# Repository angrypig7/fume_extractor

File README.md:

View this project on [CADLAB.io](https://cadlab.io/project/2056). 

# fume_extractor
portable soldering fume extractor

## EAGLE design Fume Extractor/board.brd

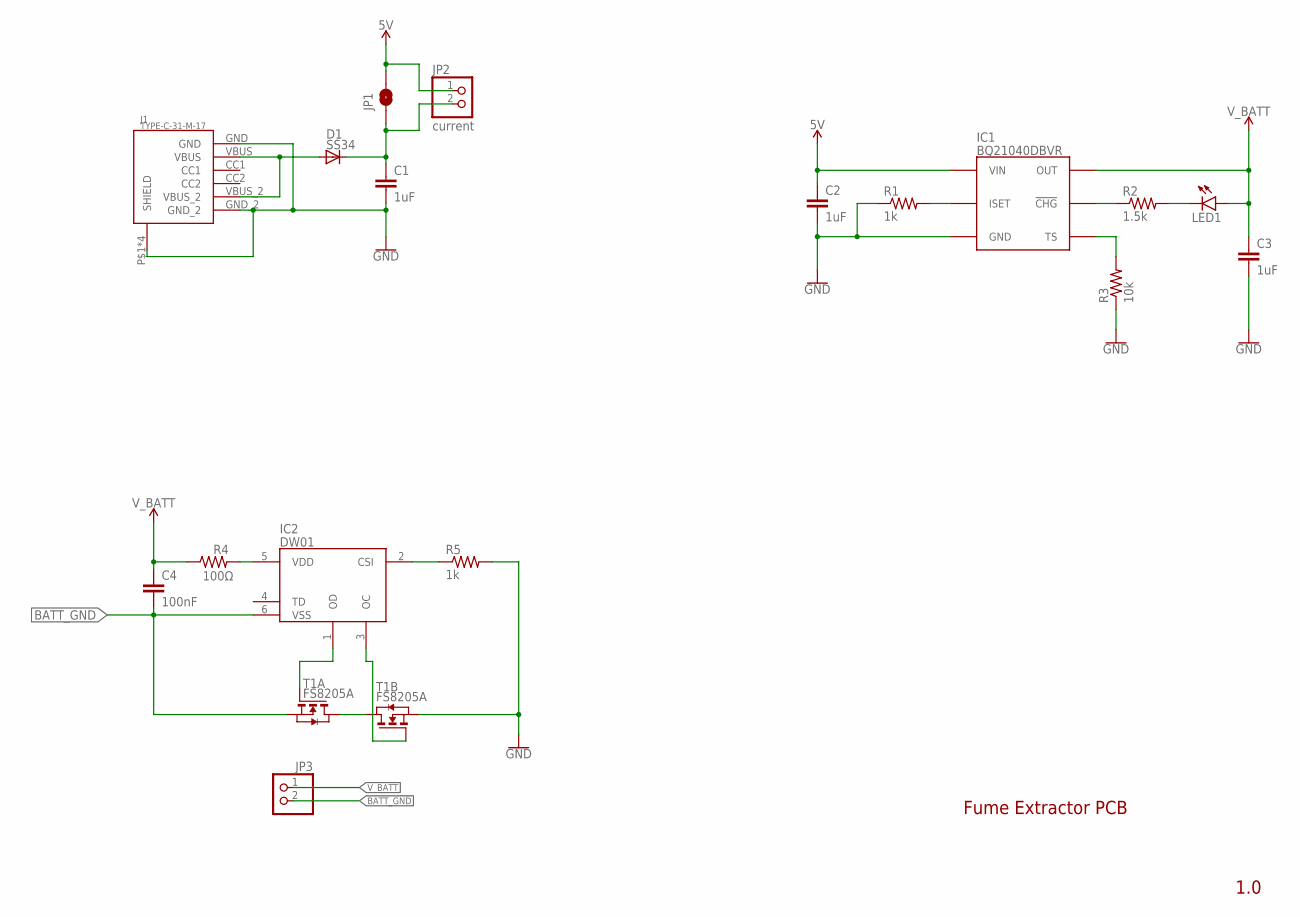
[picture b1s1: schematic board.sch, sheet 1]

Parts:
C1, C2, C3: 1uF; C0603
C4: 100nF; C0603
D1: SS34; DO214AC
IC1: BQ21040DBVR; SOT95P280X145-6N
IC2: DW01; SOT95P280X135-6N
J1: TYPE-C-31-M-17
JP1: JUMPER-SMT_2_NO_NO-SILK; SMT-JUMPER_2_NO_NO-SILK
JP2: current; 1X02/OCT
JP3: PINHD-1X2/OCT; 1X02/OCT
LED1: LEDCHIP-LED0805; CHIP-LED0805
R1, R5: 1k; R0603
R2: 1.5k; R0603
R3: 10k; R0603
R4: 100Ω; R0603
T1: FS8205A; TSSOP-8

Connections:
5V: C2.1, IC1.6 (VIN), JP1.2, JP2.1; also elsewhere on the board
BATT_GND: C4.2, IC2.6 (VSS), JP3.2, T1.2 (S), T1.3 (S)
GND: C1.2, C2.2, C3.2, IC1.5 (GND), J1.GND, J1.GND_2, J1.P$1 (SHIELD), J1.P$2 (SHIELD), J1.P$3 (SHIELD), J1.P$4 (SHIELD), R1.1, R3.1, R5.2, T1.6 (S), T1.7 (S); also elsewhere on the board
unnamed: IC2.5 (VDD), R4.2
unnamed: IC1.1 (TS), R3.2
unnamed: IC1.3 (!CHG), R2.1
unnamed: IC2.2 (CSI), R5.1
unnamed: T1.1 (D), T1.8 (D)
unnamed: IC2.1 (OD), T1.4 (G)
unnamed: IC2.3 (OC), T1.5 (G)
unnamed: LED1.C, R2.2
unnamed: IC1.4 (ISET), R1.2
unnamed: C1.1, D1.C, JP1.1, JP2.2
unnamed: D1.A, J1.VBUS, J1.VBUS_2
V_BATT: C3.1, C4.1, IC1.2 (OUT), JP3.1, LED1.A, R4.1

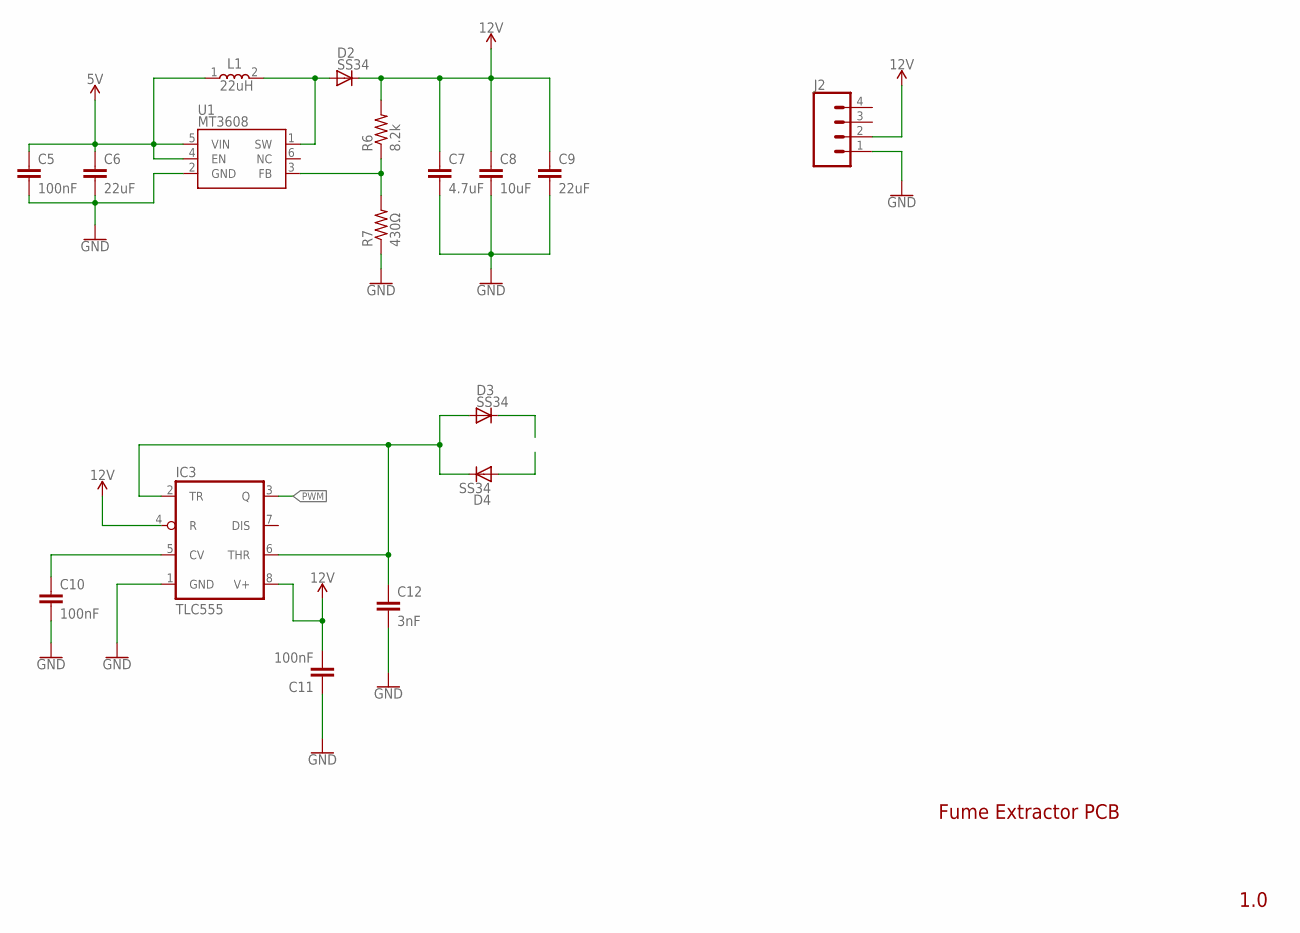
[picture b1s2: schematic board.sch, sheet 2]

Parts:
C5, C10, C11: 100nF; C0603
C6, C9: 22uF; C0805
C7: 4.7uF; C0603
C8: 10uF; C0805
C12: 3nF; C0603
D2, D3, D4: SS34; DO214AC
IC3: TLC555; SO08
J2: CONN_04POLAR_LOCK; MOLEX-1X4_LOCK
L1: 22uH; INDPM7066X300N
R6: 8.2k; R0603
R7: 430Ω; R0603
U1: MT3608; SOT23-6

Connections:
5V: C5.1, C6.1, L1.1, U1.4 (EN), U1.5 (VIN); also elsewhere on the board
12V: C7.1, C8.1, C9.1, C11.2, D2.C, IC3.4 (R), IC3.8 (V+), J2.2, R6.2
GND: C5.2, C6.2, C7.2, C8.2, C9.2, C10.2, C11.1, C12.2, IC3.1 (GND), J2.1, R7.1, U1.2 (GND); also elsewhere on the board
unnamed: D2.A, L1.2, U1.1 (SW)
unnamed: C10.1, IC3.5 (CV)
unnamed: R6.1, R7.2, U1.3 (FB)
unnamed: C12.1, D3.A, D4.C, IC3.2 (TR), IC3.6 (THR)
PWM: IC3.3 (Q)

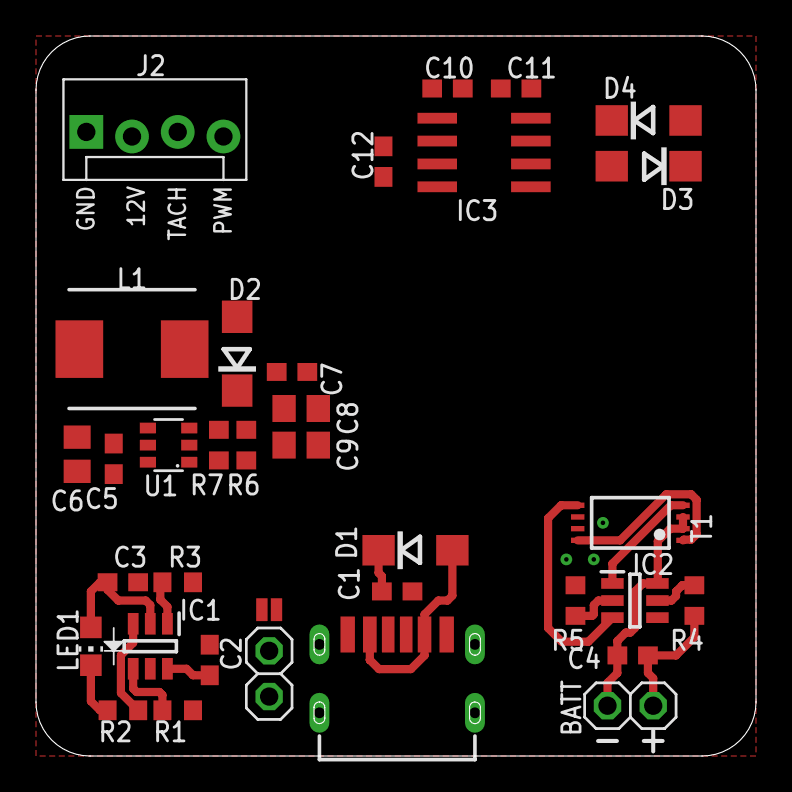
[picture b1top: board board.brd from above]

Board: 2 copper layers, 40.0 x 40.0 mm, 35 parts (0 on the bottom side), 20 nets.

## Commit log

2019-07-27 battery charging circuit
2019-07-28 battery charging + protection circuit
2019-08-14 MCP72831 circuit backup, TP4056
2019-08-14 TP4056 + DW01 + Type C input
2019-08-22 Backlink to CADLAB.io has been added.
2019-08-22 MT3608 boost converter circuit complete..?
2020-03-07 moving to BQ2104DBVR charging IC, backed up TP4056 circuit
2020-03-07 added PCB design
2020-03-07 PCB layout update
2020-03-09 PCB layout update;

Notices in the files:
parts and their libraries:
SparkFun-Jumpers: Licensing: Creative Commons ShareAlike 4.0 International - https://creativecommons.org/licenses/by-sa/4.0
